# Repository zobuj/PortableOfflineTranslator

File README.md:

# Portable Offline Translator

Portable Offline Translator is a lightweight, offline translation tool designed for quick and easy translations without the need for an internet connection. 

Lab Notebooks are located in the [`doc/notebooks/`](./doc/notebooks/) directory.

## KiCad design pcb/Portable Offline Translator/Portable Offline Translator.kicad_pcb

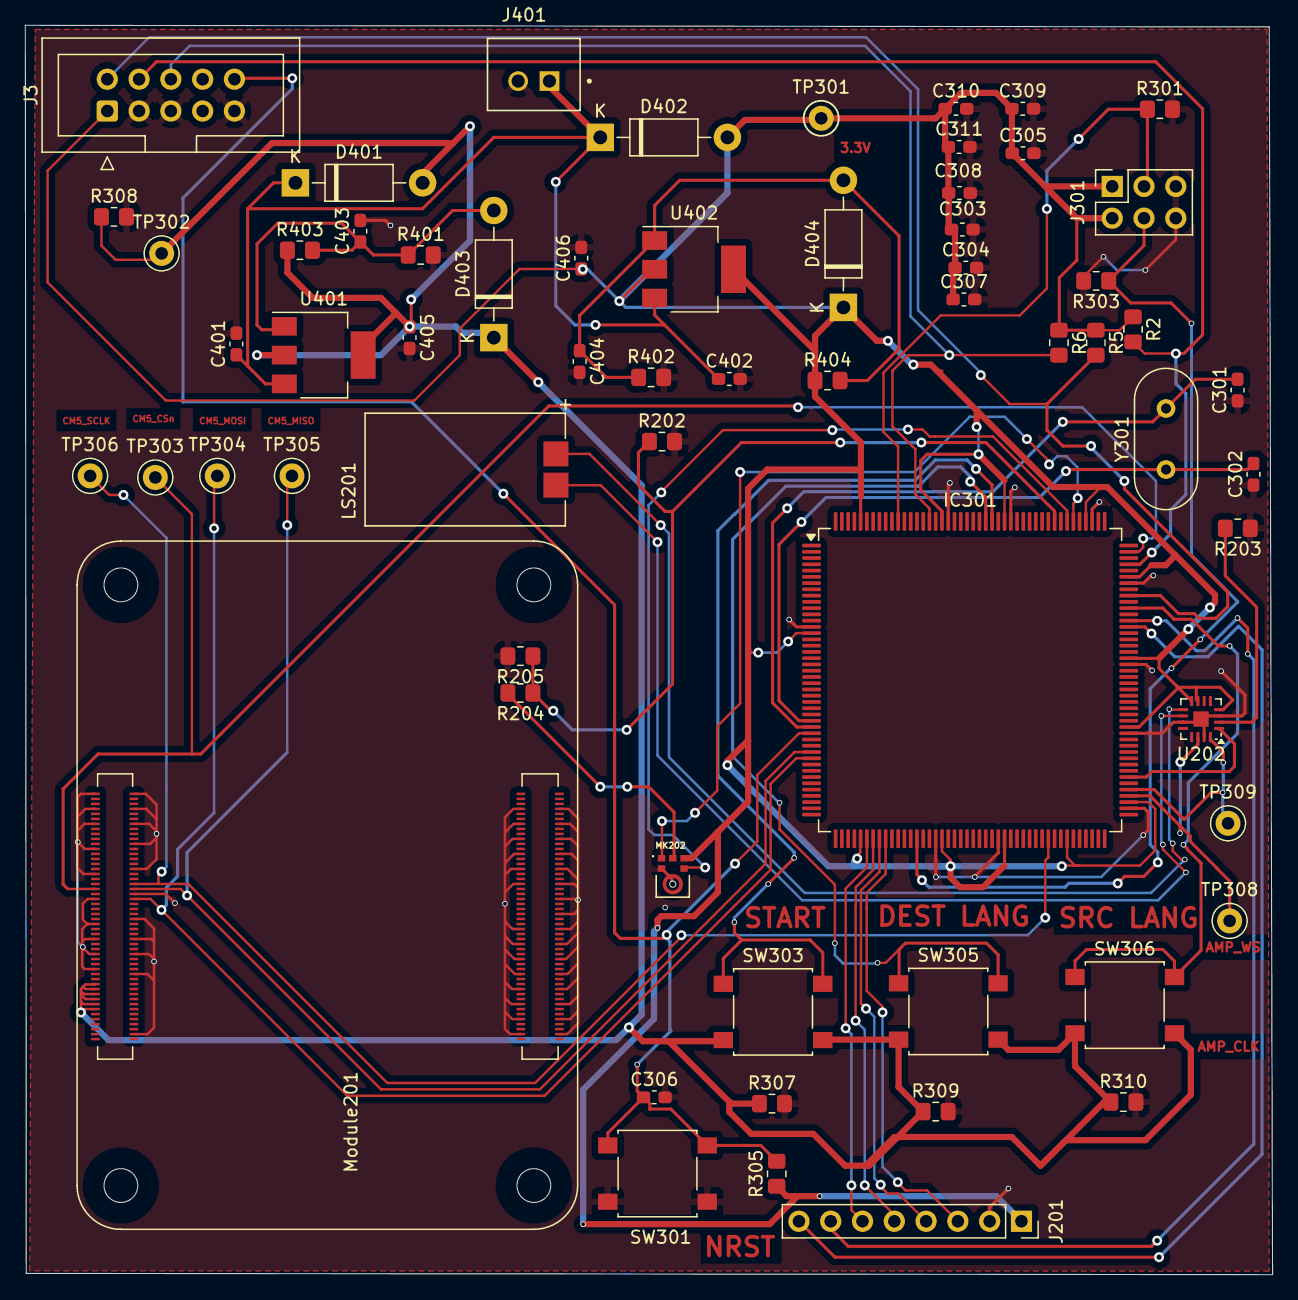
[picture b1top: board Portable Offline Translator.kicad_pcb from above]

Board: 2 copper layers, 99.7 x 99.8 mm, 63 parts (0 on the bottom side), 37 nets.

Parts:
C301, C302: 20p; C_0603_1608Metric_Pad1.08x0.95mm_HandSolder
C303, C304, C305, C307, C308: 100n; C_0603_1608Metric_Pad1.08x0.95mm_HandSolder
C306, C311: 1u; C_0603_1608Metric_Pad1.08x0.95mm_HandSolder
C309: 4.7u; C_0603_1608Metric_Pad1.08x0.95mm_HandSolder
C310: 10n; C_0603_1608Metric_Pad1.08x0.95mm_HandSolder
C401, C402: 0.1uF; C_0603_1608Metric_Pad1.08x0.95mm_HandSolder
C403, C404: 10u; C_0603_1608Metric_Pad1.08x0.95mm_HandSolder
C405, C406: 1uF; C_0603_1608Metric_Pad1.08x0.95mm_HandSolder
D401, D402, D403, D404: 1N4002; D_DO-41_SOD81_P10.16mm_Horizontal
IC301: STM32F407IET6; LQFP-176_24x24mm_P0.5mm
J3: Conn_ARM_JTAG_SWD_10; IDC-Header_2x05_P2.54mm_Vertical
J201: Conn_01x08_Male; PinSocket_1x08_P2.54mm_Vertical
J301: Conn_02x03_Odd_Even; PinSocket_2x03_P2.54mm_Vertical
J401: B2B-XH-A; JST_B2B-XH-A
LS201: CMS-16098A-SP; CUI_CMS-16098A-SP
MK202: SPH0645LM4H-B; MIC_SPH0645LM4H-B
Module201: ComputeModule5-CM5; Raspberry-Pi-5-Compute-Module
R2, R5, R6, R202, R203, R205: 100k; R_0805_2012Metric_Pad1.20x1.40mm_HandSolder
R204: 51; R_0805_2012Metric_Pad1.20x1.40mm_HandSolder
R301, R303, R305, R307, R308, R309, R310: 10k; R_0805_2012Metric_Pad1.20x1.40mm_HandSolder
R401: 1k; R_0805_2012Metric_Pad1.20x1.40mm_HandSolder
R402: 542; R_0805_2012Metric_Pad1.20x1.40mm_HandSolder
R403, R404: 330; R_0805_2012Metric_Pad1.20x1.40mm_HandSolder
SW301, SW303, SW305, SW306: SW_Push; SW_SPST_B3S-1000
TP301, TP309: 3.3V; TestPoint_Keystone_5000-5004_Miniature
TP302: 5V; TestPoint_Keystone_5000-5004_Miniature
TP303: SPI4_CSn; TestPoint_Keystone_5000-5004_Miniature
TP304: SPI4_MOSI; TestPoint_Keystone_5000-5004_Miniature
TP305: SPI4_MISO; TestPoint_Keystone_5000-5004_Miniature
TP306: SPI4_SCLK; TestPoint_Keystone_5000-5004_Miniature
TP308: I2S_CLK; TestPoint_Keystone_5000-5004_Miniature
U202: MAX98357AETE_T; TQFN-16-1EP_3x3mm_P0.5mm_EP1.23x1.23mm
U401, U402: LM317_SOT-223; SOT-223-3_TabPin2
Y301: Crystal; Crystal_HC49-U_Vertical

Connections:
+3.3V: C303.1, C304.1, C305.1, C307.1, C308.1, C309.1, C310.1, C311.1, C406.1, D402.2 (A), D404.1 (K), IC301.15 (VDD_1), IC301.49 (VDD_4), IC301.62 (VDD_5), IC301.72 (VDD_6), IC301.82 (VDD_7), IC301.91 (VDD_8), IC301.103 (VDD_9), IC301.114 (VDD_10), IC301.127 (VDD_11), IC301.136 (VDD_12), IC301.149 (VDD_13), IC301.159 (VDD_14), IC301.172 (VDD_15), J3.1 (VTref), J201.1, J301.1, J301.2, MK202.5 (VDD), R2.1, R5.1, R6.1, R305.1, R404.1, TP301.1, U202.4 (SD_MODE), U202.7 (VDD), U202.8 (VDD__1), U402.2 (VO)
+5V: C405.1, D401.2 (A), D403.1 (K), Module201.77 (+5v_(Input)), Module201.79 (+5v_(Input)), Module201.81 (+5v_(Input)), Module201.83 (+5v_(Input)), Module201.85 (+5v_(Input)), Module201.87 (+5v_(Input)), R307.1, R308.1, R309.1, R310.1, R403.1, SW303.2, SW305.2, SW306.2, TP302.1, U401.2 (VO)
/IO Circuits/AMP_I2S2_CK: IC301.93 (PB13), TP309.1, U202.16 (BCLK)
/IO Circuits/AMP_I2S2_SD: IC301.95 (PB15), U202.1 (DIN)
/IO Circuits/AMP_I2S2_WS: IC301.92 (PB12), TP308.1, U202.14 (LRCLK)
/IO Circuits/LCD_Data/Command: IC301.120 (PA9), J201.7
/IO Circuits/LCD_RST: IC301.119 (PA8), J201.8
/IO Circuits/MIC_I2S3_SCK: IC301.139 (PC10), MK202.4 (BCLK)
/IO Circuits/MIC_I2S3_SD: IC301.141 (PC12), R202.1, R204.1, R205.1
/IO Circuits/MIC_I2S3_WS: IC301.138 (PA15), MK202.1 (WS)
/IO Circuits/OUTN: LS201.N, U202.10 (OUTN)
/IO Circuits/OUTP: LS201.P, U202.9 (OUTP)
/IO Circuits/SPI1_MOSI: IC301.53 (PA7), J201.3
/IO Circuits/SPI1_NSS: IC301.50 (PA4), J201.6
/IO Circuits/SPI1_SCK: IC301.51 (PA5), J201.5
/IO Circuits/SPI4_CSn: IC301.131 (PI0), Module201.39 (GPIO8), TP303.1
/IO Circuits/SPI4_MISO: IC301.34 (PC2), Module201.40 (GPIO9), TP305.1
/IO Circuits/SPI4_MOSI: IC301.35 (PC3), Module201.44 (GPIO10), TP304.1
/IO Circuits/SPI4_SCLK: IC301.79 (PB10), Module201.38 (GPIO11), TP306.1
/IO Circuits/SPI_MISO: IC301.52 (PA6), J201.4
/MCU/JTCK/SWCLK: IC301.129 (PH14), J3.4 (SWDCLK/TCK), R2.2
/MCU/JTDO/TRACESWO: IC301.161 (PB3), J3.6 (SWO/TDO), R6.2
/MCU/JTMS/SWDIO: IC301.124 (PA13), J3.2 (SWDIO/TMS), R5.2
/MCU/NRST: C306.1, IC301.31 (NRST), J3.10 (~RESET), R305.2, SW301.2
/MCU/OSC_IN: C302.2, IC301.29 (PH0), Y301.1
/MCU/OSC_OUT: C301.2, IC301.30 (PH1), Y301.2
/PowerSS/REG_IN: C401.1, C402.1, D401.1 (K), D402.1 (K), J401.1, U401.3 (VI), U402.3 (VI)
BOOT0: IC301.166 (BOOT0), J301.3, R301.1
BOOT1: IC301.58 (PB2), J301.4, R303.1
GND: C301.1, C302.1, C303.2, C304.2, C305.2, C306.2, C307.2, C308.2, C309.2, C310.2, C311.2, C401.2, C402.2, C403.2, C404.2, C405.2, C406.2, IC301.14 (VSS_1), IC301.61 (VSS_3), IC301.71 (VSS_4), IC301.90 (VSS_5), IC301.102 (VSS_6), IC301.113 (VSS_7), IC301.126 (VSS_8), IC301.135 (VSS_9), IC301.148 (VSS_10), IC301.158 (VSS_11), J3.3 (GND), J3.5 (GND), J3.9 (GNDDetect), J201.2, J301.5, J301.6, J401.2, MK202.2 (SELECT), MK202.3 (GND), Module201.1 (GND), Module201.2 (GND), Module201.7 (GND), Module201.8 (GND), Module201.13 (GND), Module201.14 (GND), Module201.22 (GND), Module201.23 (GND), Module201.32 (GND), Module201.33 (GND), Module201.42 (GND), Module201.43 (GND), Module201.52 (GND), Module201.53 (GND), Module201.59 (GND), Module201.60 (GND), Module201.65 (GND), Module201.66 (GND), Module201.71 (GND), Module201.74 (GND), Module201.98 (GND), Module201.107 (GND), Module201.108 (GND), Module201.113 (GND), Module201.114 (GND), Module201.119 (GND), Module201.120 (GND), Module201.125 (GND), Module201.126 (GND), Module201.131 (GND), Module201.132 (GND), Module201.137 (GND), Module201.138 (GND), Module201.144 (GND), Module201.150 (GND), Module201.155 (GND), Module201.156 (GND), Module201.161 (GND), Module201.162 (GND), Module201.167 (GND), Module201.168 (GND), Module201.173 (GND), Module201.174 (GND), Module201.179 (GND), Module201.180 (GND), Module201.185 (GND), Module201.186 (GND), Module201.191 (GND), Module201.192 (GND), Module201.197 (GND), Module201.198 (GND), R202.2, R203.1, R205.2, R301.2, R303.2, R307.2, R308.2, R309.2, R310.2, R401.2, R402.2, SW301.1, U202.3 (GND), U202.11 (GND__1), U202.15 (GND__2), U202.17 (EP)
unnamed: C403.1, D403.2 (A), R401.1, R403.2, U401.1 (ADJ)
unnamed: C404.1, D404.2 (A), R402.1, R404.2, U402.1 (ADJ)
unnamed: IC301.122 (PA11), SW306.1
unnamed: IC301.151 (PD7), SW303.1
unnamed: IC301.152 (PG9), SW305.1
unnamed: MK202.6 (DATA_OUT), R204.2
unnamed: R203.2, U202.2 (GAIN_SLOT)

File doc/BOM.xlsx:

BOM
Id | Designator | Package | Quantity | Designation | Price per Piece ($)
1 | D403,D401,D404,D402 | D_DO-41_SOD81_P10.16mm_Horizontal | 4 | 1N4002 | 0.2
2 | R303,R305,R306,R307,R301 | R_0805_2012Metric_Pad1.20x1.40mm_HandSolder | 5 | 10k | 0.1
3 | J201 | PinSocket_1x10_P2.54mm_Vertical | 1 | Conn_01x10_Female | 0.56000000000000005
4 | C401,C402 | C_0603_1608Metric_Pad1.08x0.95mm_HandSolder | 2 | 0.1uF | 0.49
5 | SW301,SW303,SW302 | SW_SPST_B3S-1000 | 3 | SW_Push | 0.56999999999999995
6 | U401,U402 | SOT-223-3_TabPin2 | 2 | LM317_SOT-223 | 0.64
8 | LS201 | CUI_CMS-16098A-SP | 1 | CMS-16098A-SP | 2.41
9 | C309 | C_0603_1608Metric_Pad1.08x0.95mm_HandSolder | 1 | 4.7u | 0.49
10 | C307,C303,C304,C305,C308 | C_0603_1608Metric_Pad1.08x0.95mm_HandSolder | 5 | 100n | 0.49
11 | U301 | UFBGA-201_10x10mm_Layout15x15_P0.65mm | 1 | STM32F407IEHx | 12.07
12 | U201 | 21-0896B_9_MXM | 1 | MAX98357AEWL+T | 4.3
13 | MK201 | MIC_ICS-43434 | 1 | ICS-43434 | 3.12
14 | C404,C403 | C_0603_1608Metric_Pad1.08x0.95mm_HandSolder | 2 | 10u | 0.49
15 | C301,C302 | C_0603_1608Metric_Pad1.08x0.95mm_HandSolder | 2 | 20p | 0.49
16 | R201,R202 | R_0805_2012Metric_Pad1.20x1.40mm_HandSolder | 2 | 100k | 0.1
17 | C311,C306 | C_0603_1608Metric_Pad1.08x0.95mm_HandSolder | 2 | 1u | 0.49
18 | R302,R304 | R_0805_2012Metric_Pad1.20x1.40mm_HandSolder | 2 | 2k2 | 0.1
19 | C310 | C_0603_1608Metric_Pad1.08x0.95mm_HandSolder | 1 | 10n | 0.49
20 | J301 | PinSocket_2x03_P2.54mm_Vertical | 1 | Conn_02x03_Odd_Even | 0.56000000000000005
21 | Y301 | Crystal_HC49-U_Vertical | 1 | Crystal | 52
22 | R401 | R_0805_2012Metric_Pad1.20x1.40mm_HandSolder | 1 | 1k | 0.1
23 | R403,R404 | R_0805_2012Metric_Pad1.20x1.40mm_HandSolder | 2 | 330 | 0.1
25 | C406,C405 | C_0603_1608Metric_Pad1.08x0.95mm_HandSolder | 2 | 1uF | 0.49
26 | BT401 | BAT_1048P | 1 | 1048P | 10.77
27 | R402 | R_0805_2012Metric_Pad1.20x1.40mm_HandSolder | 1 | 542 | 0.1
 | CM5 | Raspberry Pi Compute Module 5 | 1 | CM5 | 80
 | CM5 Expansion Board | GPIO Expansion board for CM5 | 1 | CM5 Expander | 20
 |  |  |  | Total | 199.20999999999998

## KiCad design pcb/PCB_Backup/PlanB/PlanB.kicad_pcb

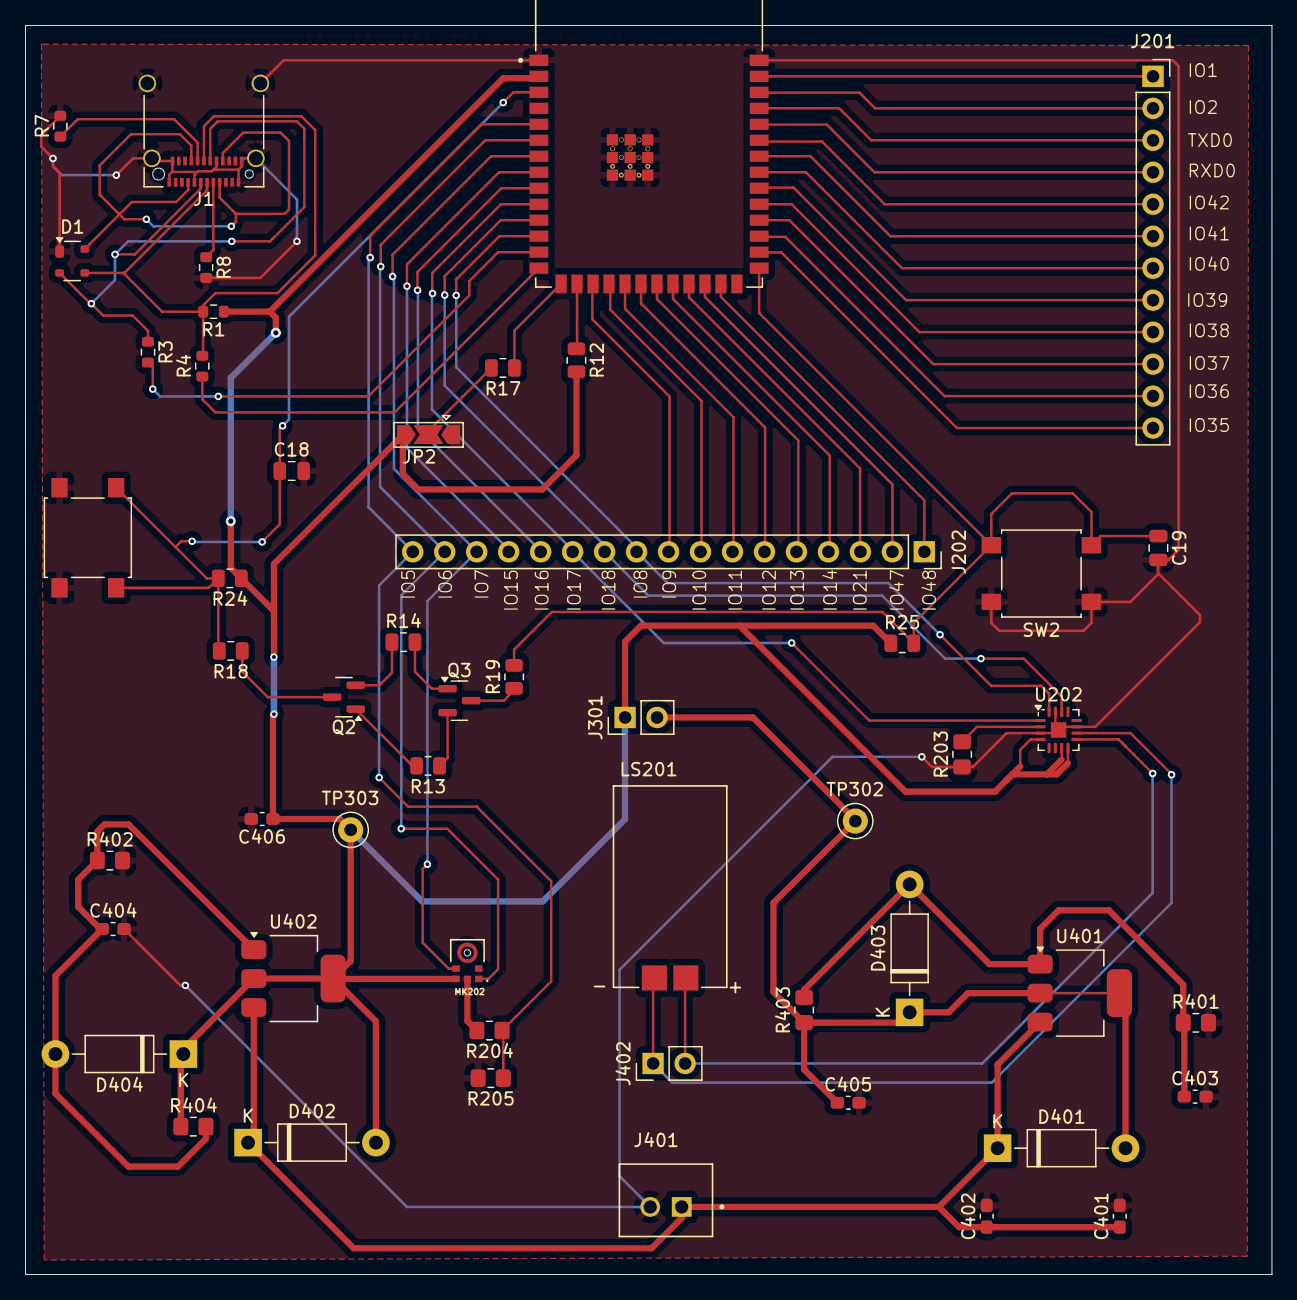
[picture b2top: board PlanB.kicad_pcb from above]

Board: 2 copper layers, 99.0 x 99.2 mm, 52 parts (0 on the bottom side), 57 nets.

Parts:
C18, C19: 1u; C_0805_2012Metric
C401, C402: 0.1uF; C_0603_1608Metric_Pad1.08x0.95mm_HandSolder
C403, C404: 10u; C_0603_1608Metric_Pad1.08x0.95mm_HandSolder
C405, C406: 1uF; C_0603_1608Metric_Pad1.08x0.95mm_HandSolder
D1: SP0503BAHT; SOT-143
D401, D402, D403, D404: 1N4002; D_DO-41_SOD81_P10.16mm_Horizontal
J1: USB_C_Receptacle_USB2.0; USB_C_Receptacle_Amphenol_12401610E4-2A_CircularHoles
J201: Conn_01x12_Pin; PinSocket_1x12_P2.54mm_Vertical
J202: Conn_01x17_Pin; PinSocket_1x17_P2.54mm_Vertical
J301, J402: Conn_01x02_Pin; PinHeader_1x02_P2.54mm_Vertical
J401: B2B-XH-A; JST_B2B-XH-A
JP2: SolderJumper_3_Open; SolderJumper-3_P2.0mm_Open_TrianglePad1.0x1.5mm
LS201: CMS-16098A-SP; CUI_CMS-16098A-SP
MK202: SPH0645LM4H-B; MIC_SPH0645LM4H-B
Q2, Q3: SS8050-G; SOT-23
R1: 1.5k; R_0603_1608Metric
R3, R4: 22; R_0603_1608Metric
R7, R8: 5.1k; R_0603_1608Metric
R12, R17: 1k; R_0805_2012Metric
R13, R14, R18, R19: 10k; R_0805_2012Metric
R24, R25: 100k; R_0805_2012Metric
R203, R205: 100k; R_0805_2012Metric_Pad1.20x1.40mm_HandSolder
R204: 51; R_0805_2012Metric_Pad1.20x1.40mm_HandSolder
R401: 1k; R_0805_2012Metric_Pad1.20x1.40mm_HandSolder
R402: 542; R_0805_2012Metric_Pad1.20x1.40mm_HandSolder
R403, R404: 330; R_0805_2012Metric_Pad1.20x1.40mm_HandSolder
SW1, SW2: SW_Push; SW_SPST_B3S-1000
TP302: 5V; TestPoint_Keystone_5000-5004_Miniature
TP303: 3.3V; TestPoint_Keystone_5000-5004_Miniature
U201: ESP32-S3-WROOM-1-N8R8; XCVR_ESP32S3WROOM1N8R8
U202: MAX98357AETE_T; TQFN-16-1EP_3x3mm_P0.5mm_EP1.23x1.23mm
U401, U402: LM317_SOT-223; SOT-223-3_TabPin2

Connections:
+3.3V: C406.1, D402.2 (A), D404.1 (K), J301.1, JP2.3 (B), MK202.5 (VDD), R1.1, R12.2, R24.1, R25.1, R404.1, TP303.1, U201.2 (3V3), U202.4 (SD_MODE), U202.7 (VDD), U202.8 (VDD__1), U402.2 (VO)
+5V: C405.1, D401.2 (A), D403.1 (K), J301.2, R403.1, TP302.1, U401.2 (VO)
/IO/OUTN: J402.1, LS201.N, U202.10 (OUTN)
/IO/OUTP: J402.2, LS201.P, U202.9 (OUTP)
/MCU/CHIP_PU: C18.1, R18.2, R24.2, SW1.2, U201.3 (EN)
/MCU/D+: R4.1, U201.14 (IO20)
/MCU/D-: R3.2, U201.13 (IO19)
/MCU/DTR: Q3.2 (E), R13.1
/MCU/EXT_D+: D1.3 (K), J1.A6 (D+), J1.B6 (D+), R1.2, R4.2
/MCU/EXT_D-: D1.2 (K), J1.A7 (D-), J1.B7 (D-), R3.1
/MCU/GPIO0_STRAPPING: C19.1, R19.2, R25.2, SW2.2, U201.27 (IO0)
/MCU/GPIO3_STRAPPING: R17.1, U201.15 (IO3)
/MCU/GPIO46_STRAPPING: R12.1, U201.16 (IO46)
/MCU/IO1: J201.1, U201.39 (IO1)
/MCU/IO2: J201.2, U201.38 (IO2)
/MCU/IO5: J202.17, R204.1, R205.1, U201.5 (IO5)
/MCU/IO6: J202.16, MK202.1 (WS), U201.6 (IO6)
/MCU/IO7: J202.15, MK202.4 (BCLK), U201.7 (IO7)
/MCU/IO8: J202.10, U201.12 (IO8), U202.16 (BCLK)
/MCU/IO9: J202.9, U201.17 (IO9)
/MCU/IO10: J202.8, U201.18 (IO10)
/MCU/IO11: J202.7, U201.19 (IO11)
/MCU/IO12: J202.6, U201.20 (IO12)
/MCU/IO13: J202.5, U201.21 (IO13)
/MCU/IO14: J202.4, U201.22 (IO14)
/MCU/IO15: J202.14, U201.8 (IO15)
/MCU/IO16: J202.13, U201.9 (IO16)
/MCU/IO17: J202.12, U201.10 (IO17), U202.1 (DIN)
/MCU/IO18: J202.11, U201.11 (IO18), U202.14 (LRCLK)
/MCU/IO21: J202.3, U201.23 (IO21)
/MCU/IO35: J201.12, U201.28 (IO35)
/MCU/IO36: J201.11, U201.29 (IO36)
/MCU/IO37: J201.10, U201.30 (IO37)
/MCU/IO38: J201.9, U201.31 (IO38)
/MCU/IO39: J201.8, U201.32 (IO39)
/MCU/IO40: J201.7, U201.33 (IO40)
/MCU/IO41: J201.6, U201.34 (IO41)
/MCU/IO42: J201.5, U201.35 (IO42)
/MCU/IO47: J202.2, U201.24 (IO47)
/MCU/IO48: J202.1, U201.25 (IO48)
/MCU/RTS: Q2.2 (E), R14.1
/MCU/RXD0: J201.4, U201.36 (RXD0)
/MCU/TXD0: J201.3, U201.37 (TXD0)
/MCU/V_USB: D1.4 (K), J1.A4 (VBUS), J1.A9 (VBUS), J1.B4 (VBUS), J1.B9 (VBUS)
/PowerSS/REG_IN: C401.1, C402.1, D401.1 (K), D402.1 (K), J401.1, U401.3 (VI), U402.3 (VI)
GND: C18.2, C19.2, C401.2, C402.2, C403.2, C404.2, C405.2, C406.2, D1.1 (A), J1.A1 (GND), J1.A8 (SBU1), J1.A12 (GND), J1.B1 (GND), J1.B8 (SBU2), J1.B12 (GND), J1.S1 (SHIELD), J401.2, JP2.1 (A), MK202.2 (SELECT), MK202.3 (GND), R7.2, R8.2, R203.1, R205.2, R401.2, R402.2, SW1.1, SW2.1, U201.1 (GND), U201.40 (GND__1), U201.41_1 (GND__2), U201.41_2 (GND__3), U201.41_3 (GND__4), U201.41_4 (GND__5), U201.41_5 (GND__6), U201.41_6 (GND__7), U201.41_7 (GND__8), U201.41_8 (GND__9), U201.41_9 (GND__10), U202.3 (GND), U202.11 (GND__1), U202.15 (GND__2), U202.17 (EP)
unnamed: C403.1, D403.2 (A), R401.1, R403.2, U401.1 (ADJ)
unnamed: C404.1, D404.2 (A), R402.1, R404.2, U402.1 (ADJ)
unnamed: J1.A5 (CC1), R8.1
unnamed: J1.B5 (CC2), R7.1
unnamed: JP2.2 (C), R17.2
unnamed: MK202.6 (DATA_OUT), R204.2
unnamed: Q2.1 (B), R13.2
unnamed: Q2.3 (C), R18.1
unnamed: Q3.1 (B), R14.2
unnamed: Q3.3 (C), R19.1
unnamed: R203.2, U202.2 (GAIN_SLOT)

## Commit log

2025-02-06 MCU documentation
2025-02-06 Raspberry Pi CM documentation
2025-02-06 Amplifier Documentation
2025-02-06 Microphone Documentation
2025-02-06 moved all of the documents to the doc folder
2025-02-06 added read me and then formatted some of the folders
2025-02-06 adding a basic src dir
2025-02-11 made changes to the rspcm
2025-02-11 added submodule repo
2025-02-11 you can test the voice recog
2025-02-11 rename
2025-02-11 removed
2025-02-11 Removed broken submodule
2025-02-11 Re-added submodule
2025-02-11 draft block diagram
2025-02-11 adding RFA
2025-02-11 restructured git repo
2025-02-11 Power SS added to drawio
2025-02-11 added lab notebook
2025-02-11 high level requirements done?
2025-02-11 adding to hlr
2025-02-11 added requirements
2025-02-11 Reconfiugured Repo
2025-02-11 adding proposal
2025-02-11 adding gitignore
2025-02-11 resolved notebooks
2025-02-11 resolved notebooks agagin
2025-02-11 Rename proposal.md to README.md
2025-02-11 Rename RFA.md to README.md
2025-02-14 Updated LDO on blk dia
2025-02-14 updated doc
2025-02-14 mdouels
2025-02-19 Interrupt Based Driven pipeline working, build system is setup aswell
2025-02-20 First transcription done from sample.pcm
2025-02-20 changed to 24 bit and now have some framework for debugging the speech
2025-02-20 up to date
2025-02-20 fixed req
2025-02-20 added translation
2025-02-20 removed build
2025-02-20 removed marian
2025-02-20 adding rebuild file
2025-02-21 Refactored
2025-02-21 IT FINALLY WORKS ALL INTEGRATED
2025-02-21 Removed config
2025-02-25 working with speech
2025-02-25 fixed everything with speaker
2025-02-25 fixed speaker init
2025-02-25 fixed exec
2025-02-26 Added KiCad files
2025-02-26 KiCad files added pt2
2025-02-27 MCU and Power SS updated
2025-02-27 integration of the MCU kind of working
2025-02-27 IO schematic in prog
2025-03-05 mcu communicating starting flashing of rspcm
2025-03-06 starting on UI and working on a cleaner streaming form mic
2025-03-06 ignoring build in clay
2025-03-06 usbboot changes
2025-03-07 Added Datasheets and PCB
2025-03-10 PCB Backup
2025-03-11 updating inmp code
2025-03-13 PCB iteration 1
2025-03-13 PCB iteration1 gerber and drill files added
2025-03-22 updated some content in the lcd
2025-03-22 WIP: Local changes before pulling
2025-04-03 main PCB v1 done
2025-04-06 added esp code
2025-04-08 working reading audio data
2025-04-08 wip esp
2025-04-09 IT WORKS
2025-04-09 updates from the pi
2025-04-09 adding button interrupt funcitonality
2025-04-09 removed ino file
2025-04-10 working perfectly now
2025-04-10 updated the main.py
2025-04-14 made changes to esp code and removed clay and integrated a new lcd interface
2025-04-21 made some changes to the spi interfaces
2025-04-21 currently working for display
2025-04-21 working
2025-04-22 fully working
2025-04-22 adding pcm file
2025-04-22 working on pi
2025-05-01 U DONT LIKE THAT ARNAYYYY
2025-05-05 code working on the pi
2025-05-08 lab notebook
2025-05-08 pcb_backup files
2025-05-08 Josh Notebook Added
2025-05-08 added correct lab notebook
2025-05-08 adding gitignore file
2025-05-08 mcu firmware
2025-05-08 final changes
2025-05-08 reformat git:
2025-05-08 github refactor
2025-05-08 reformatted esp code
2025-05-08 formatted main
2025-05-08 cleaned up spi interface
2025-05-08 cleaned up main
2025-05-08 cleaned makefile
2025-05-08 udpated output
